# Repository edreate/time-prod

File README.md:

# FocusDock — Focus & Availability Device

A small desk gadget that protects your focus time. It sits on your desk as a
phone dock, or clips onto the top or bottom edge of your monitor. One glance
tells you (and everyone walking by) what's going on:

- **Menu** — pick a program: Focus Timer or Available/Busy. Long-press the
  center click, from anywhere, to jump back to the menu.
- **Focus timer** — set an H:M:S duration, click to start. The screen counts
  down and the LEDs empty out like a progress bar.
- **Status light** — LEDs glow **green** (free), **red** (busy), or **amber**
  (timer running). One click toggles available/busy: an instant meeting
  indicator.
- **Phone dock** — park your phone on it and out of your hands.
- **Mounts either way up** — clip it to the top or bottom monitor edge; the
  screen flips itself the right way up automatically.

## The prototype today

Everything below is running on a breadboard right now:

**Working:** display, motion sensor, auto-flip, LED strip, the menu, focus
timer, pomodoro, and the available/busy status light.
**Not built yet:** Wi-Fi settings, enclosure, proper 5V LED power — see the
[roadmap](#roadmap).

## How to use it

The 5-way button does everything:

| Button | Menu | Setting the timer | Timer running/paused | Availability |
|---|---|---|---|---|
| **Up / Down** | Move cursor | Change selected field | Down = cancel (paused) | — |
| **Left / Right** | — | Select H / M / S field | — | — |
| **Click** (center) | Open program | Start | Pause / resume | Toggle available/busy |
| **Hold click** | — | Return to menu, from any screen | | |

When a focus session hits zero the LEDs blink green and the screen shows
*Done!* — press any button to dismiss.

## What's inside

| Part | Job | ~Price |
|---|---|---|
| ESP32-S3 board (WROOM-1 N16R8) | The brain — runs everything, provides Wi-Fi | €14.49 |
| 1.3" OLED display (128×64, I2C) | Timer and menus | €7.19 |
| BMI160 motion sensor | Detects which way up it's mounted | ~€5 |
| WS2812B LED strip | The status light | €3.89 |
| 5-way button (5DirKey) | All input | ~€1 |

Full wiring instructions, circuit diagram, and part gotchas:
**[docs/HARDWARE.md](docs/HARDWARE.md)**.
New to electronics? Every concept this project uses, explained briefly:
**[docs/ELECTRONICS.md](docs/ELECTRONICS.md)**.

## Build & flash the firmware

You need [Python 3](https://www.python.org/downloads/) and a USB-C cable.
Everything else installs itself.

1. **Plug in the board** and find its port:
   ```
   make ports
   ```
   Yours is one of the `usbmodem*` entries (not `Bluetooth-Incoming-Port` or
   `debug-console`). The board has two USB-C ports — if one doesn't respond,
   try the other. macOS can rename the port across reconnects, so re-check if
   an upload suddenly can't find it.

2. **Flash:**
   ```
   make flash PORT=/dev/cu.usbmodemXXXX
   ```
   The first run installs PlatformIO and downloads the toolchain (~2 min,
   one-time). It then uploads the firmware and opens the serial monitor so you
   can watch the device's log output. `Ctrl+C` exits the monitor.

Other targets: `make build`, `make upload`, `make monitor`, `make clean`.

**If upload hangs at "Connecting..."**: hold **BOOT**, tap **RESET**, release
**BOOT**, retry. If it fails partway with a checksum error, that's a flaky USB
connection — reseat the cable and retry.

### Test firmwares

Besides the main firmware there's a small test build for checking the
hardware — useful after wiring changes. Two boards exist during the
prototype transition (today's N16R8 devkit, and an ESP32-S3 Zero being
evaluated as a smaller replacement — see
[docs/prototype-hardware/README.md](docs/prototype-hardware/README.md)), so
`ENV` picks firmware **and** board:

| `ENV` | What it checks | Board |
|---|---|---|
| `time-prod-app-n16r8` *(default)* | The real firmware — everything | N16R8 devkit |
| `test-peripherals-n16r8` | I2C scan + display + IMU readout: is everything wired and answering? | N16R8 devkit |
| `time-prod-app-s3zero` | The real firmware | ESP32-S3 Zero |
| `test-peripherals-s3zero` | Same hardware check, on the S3 Zero — flash this first on a new S3 Zero board | ESP32-S3 Zero |

Flash it with `make flash ENV=test-peripherals-n16r8 PORT=...` (swap the
`ENV` for whichever board/firmware combination you need).

## Tweaking the firmware

Every tunable number lives in [`src/config.h`](src/config.h): pin assignments,
colors, timer defaults, thresholds. Change a value, `make flash`, done.

The code is split two ways: one header per **peripheral** in `src/hardware/`,
one header per **program** in `src/software/`. `main.cpp` is just the shell —
it owns no hardware and no program state, it routes button events to whichever
program is open and asks it to render.

Adding a sensor is one header in `src/hardware/`; adding a program is one
header in `src/software/` plus a menu row. No build config to touch either way.

Project layout:

```
src/config.h              every tunable (pins, colors, thresholds)
src/hardware/display.h    OLED panel
src/hardware/leds.h       WS2812B status light
src/hardware/imu.h        accelerometer -> screen orientation
src/hardware/buttons.h    5-way switch, debounced
src/software/timer.h      focus timer program
src/software/pomodoro.h   pomodoro program
src/software/availability.h  available / busy program
src/main.cpp              the shell: menu, dispatch, loop
src/test_peripherals.cpp  peripheral check test build
platformio.ini      build configuration (one env per firmware x board)
Makefile            build/upload/monitor shortcuts
docs/HARDWARE.md    parts, wiring, circuit diagram
docs/ELECTRONICS.md electronics concepts, briefly explained
```

## Roadmap

What it takes to go from breadboard to a product with a long life:

**Hardware**
- [ ] Powered by USB only — no battery, no dual-power diode needed
  - [ ] Move LED strip to proper 5V power + 74AHCT125 level shifter +
        1000 µF cap (required at the current 10-LED count, not just at
        scale — exact specs: [HARDWARE.md](docs/HARDWARE.md#level-shifter--capacitor---exact-specs))
- [ ] Supports up to 10 LEDs at max brightness, on a USB 3.0 port (~700-750mA
      draw against USB 3.0's 900mA — see Power notes in HARDWARE.md)
- [ ] Custom PCB once the design settles

**Firmware**
- [ ] One button to instantly switch between available and busy
- [x] Pomodoro program (work / short break / long break, auto-cycling)
- [ ] Settings page over the device's own Wi-Fi hotspot, saved across power-off.
      **Wi-Fi defaults OFF on boot**, menu toggle to enable — its active/TX
      current isn't budgeted into the power target above by default.
- [ ] Wi-Fi client mode (optional, same default-off behavior)
- [ ] Factory-reset gesture (e.g. hold click 10s)
- [ ] Max-brightness LED mode as a menu setting, off by default. Default
      brightness stays at the current power-safe cap (`LED_BRIGHTNESS` in
      `src/config.h`); a menu option raises it for whoever's on a supply
      that can take it, rather than the firmware assuming one globally.
- [ ] Over-the-air firmware updates (optional)

**Product**
- [ ] Session stats (focus minutes per day/week)
- [ ] User-test with non-technical people; simplify anything they stumble on

## License

See [LICENSE](LICENSE).

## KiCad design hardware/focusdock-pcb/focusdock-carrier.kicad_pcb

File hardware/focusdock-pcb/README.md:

# FocusDock Carrier Board

A two-layer carrier PCB that replaces the breadboard wiring in
[`docs/HARDWARE.md`](../../docs/HARDWARE.md). It carries **no bare ICs** — the
ESP32-S3 devkit, OLED, IMU, LED strip and 5-way button all stay as modules and
plug into headers. The board is just the wiring, plus the one passive the
electronics doc asks for (the LED series resistor) and rail decoupling.

Open `focusdock-carrier.kicad_pro` in KiCad 8 or newer (built with 10.0.5).

| | |
|---|---|
| Size | 70 × 50 mm, 3 mm corner radius |
| Layers | 2 (F.Cu / B.Cu), GND pour on both, 59 stitching vias |
| Mounting | 4 × Ø2.7 mm (M2.5), corners |
| Trace widths | 0.25 mm signal, 0.5 mm power |
| ERC | 0 errors, 0 warnings |
| DRC | 0 errors, 0 unconnected pads |

## How the devkit mounts

The ESP32-S3-DevKitC-1 has no bundled KiCad footprint, so it is modelled as
**two 1×22 female sockets** (J1 / J3) that the devkit plugs into like a shield.
The spacing is not a guess — it was measured from Espressif's own mechanical
DXF (`DXF_ESP32-S3-DevKitC-1_V1.1_20220429.dxf`):

| Measurement | Value |
|---|---|
| Header row pitch (J1 ↔ J3) | **22.86 mm** (0.900 in) |
| Pin pitch | 2.54 mm |
| Pins per row | 22 |
| Devkit outline | 62.74 × 25.40 mm |
| Devkit drill | Ø1.02 mm |

Pin 1 of both rows is at the **antenna** end; the USB ports are at the pin-22
end. The devkit body spans roughly x 21.5–84.3, y 38.7–64.1 on this board, so
every peripheral connector sits *above* it and stays reachable once the devkit
is seated.

## Connectors

Pin 1 is the square pad on every header. Full legend is also printed on the
back silkscreen.

| Ref | Part | Pins (1 → n) |
|---|---|---|
| **J1** | Devkit socket, row J1 | `3V3 3V3 RST 4 5 6 7 15 16 17 18 8 3 46 9 10 11 12 13 14 5V G` |
| **J3** | Devkit socket, row J3 | `G TX RX 1 2 42 41 40 39 38 37 36 35 0 45 48 47 21 20 19 G G` |
| **J2** | OLED, 1×4 | `VDD GND SCK SDA` |
| **J4** | BMI160 IMU, 1×12 | `VIN NC GND SCL SDA SA0 CS NC NC NC NC NC` |
| **J5** | WS2812B strip, 1×3 | `VDD DIN GND` |
| **J6** | 5DirKey V1-2, 1×6 | `GND F B L R CLICK` |

`J6` pins are named by the button module's **physical silkscreen** (F/B/L/R),
not the logical directions the firmware uses — `buttonsPoll()` in
`src/hardware/buttons.h` does that remap. See the button-mapping section of
[`CLAUDE.md`](../../CLAUDE.md).

## Net map

Matches the wiring table in `docs/HARDWARE.md` pin for pin.

| Net | Devkit pin | Goes to |
|---|---|---|
| `+3V3` | J1/1, J1/2 | J2/1, J4/1 (VIN), J4/7 (CS, tied high for I2C mode), JP1/1, C1, C2 |
| `GND` | J1/22, J3/1, J3/21, J3/22 | pour → every module ground, J4/6 (SA0 → 0x68) |
| `I2C_SDA` | J1/12 (GPIO8) | J2/4, J4/5 |
| `I2C_SCL` | J1/15 (GPIO9) | J2/3, J4/4 |
| `LED_DATA` | J1/9 (GPIO16) | R1 (330 Ω) |
| `LED_DIN` | — | R1 → J5/2 |
| `LED_VDD` | — | JP1/2 → J5/1, C3 |
| `+5V` | J1/21 | JP1/3 |
| `BTN_F` | J1/4 (GPIO4) | J6/2 |
| `BTN_B` | J1/5 (GPIO5) | J6/3 |
| `BTN_L` | J1/6 (GPIO6) | J6/4 |
| `BTN_R` | J1/7 (GPIO7) | J6/5 |
| `BTN_CLICK` | J1/8 (GPIO15) | J6/6 |

`J4/2` (the BMI160 breakout's `3V3` pin) is deliberately left unconnected — it
is the module regulator's *output*, and driving it is the mistake
`docs/HARDWARE.md` warns about. All other IMU aux pins (INT1/INT2/OCS/SCX/SDX)
are unconnected too, as are the 19 devkit GPIOs the firmware doesn't use.

## JP1 — LED supply selector

`docs/HARDWARE.md` runs the WS2812B at 3.3 V for bring-up but notes 5 V is the
real spec. JP1 makes that a solder-jumper choice instead of a board respin:

```
  +3V3  1 ──┐
            ├── 2  LED_VDD  →  J5/1, C3
   +5V  3 ──┘
```

Ships with **1–2 bridged (3.3 V)**, matching the current firmware and docs. To
move to 5 V, cut the 1–2 bridge and solder 2–3 — and read the power note in
`docs/HARDWARE.md` first: at 5 V the 3.3 V data line is marginal and wants the
74AHCT125 level shifter that is still on the roadmap.

## Files

```
focusdock-carrier.kicad_pro/.kicad_sch/.kicad_pcb   the project
export/                                            SVG + PNG previews
fab/gerbers/                                       gerbers + Excellon drill
fab/focusdock-carrier-bom.csv                      BOM
fab/focusdock-carrier-pos.csv                      pick-and-place
```

`fab/` is generated output — regenerate it from the project rather than
editing it.

## Before you order

- **Verify the J4 pin order against your actual BMI160 breakout.** The board is
  wired for the common GY-BMI160 12-pin order listed above. Breakouts sold under
  the same name do vary; a mismatch makes that one connector wrong.
- The four `MountingHole_2.7mm` DRC warnings ("does not match copy in library")
  are cosmetic — the footprints were created as local variants.
- No enclosure dimensions were available, so the outline is a plain rounded
  rectangle sized to the devkit. The monitor-clip / phone-dock mechanics in the
  README roadmap are not accounted for.

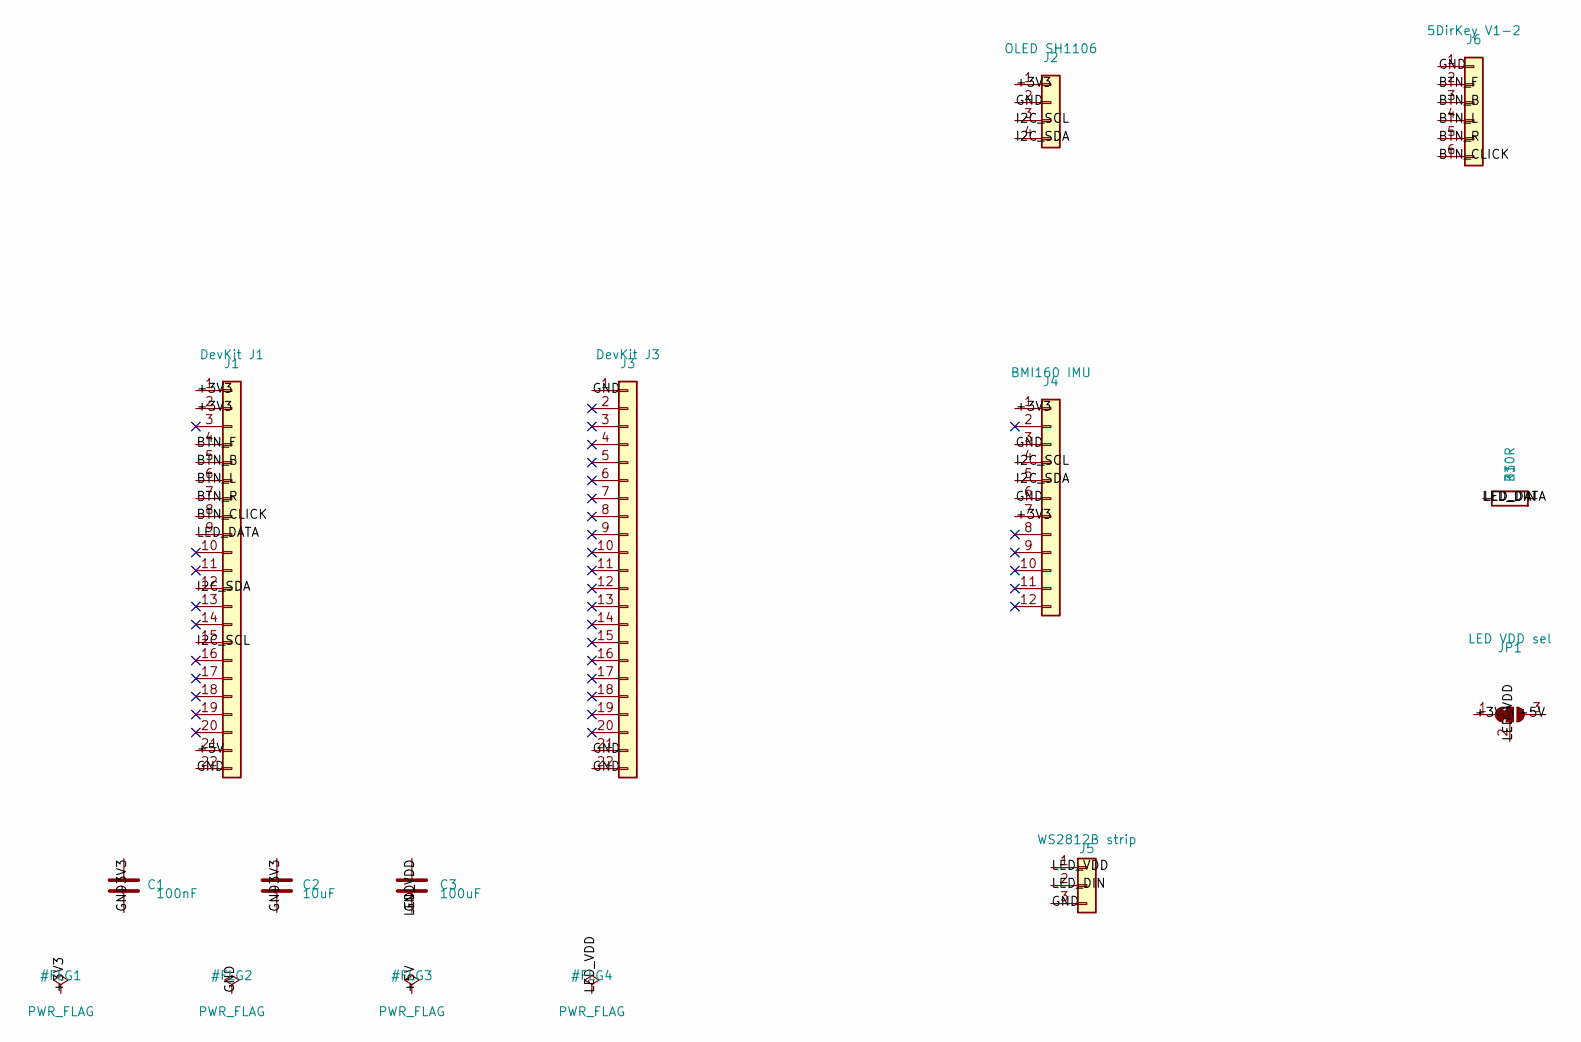
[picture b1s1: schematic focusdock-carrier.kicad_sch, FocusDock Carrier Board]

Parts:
C1: 100nF; C_0805_2012Metric
C2: 10uF; C_0805_2012Metric
C3: 100uF; C_1206_3216Metric
J1: DevKit J1; PinSocket_1x22_P2.54mm_Vertical
J2: OLED SH1106; PinSocket_1x04_P2.54mm_Vertical
J3: DevKit J3; PinSocket_1x22_P2.54mm_Vertical
J4: BMI160 IMU; PinSocket_1x12_P2.54mm_Vertical
J5: WS2812B strip; PinSocket_1x03_P2.54mm_Vertical
J6: 5DirKey V1-2; PinSocket_1x06_P2.54mm_Vertical
JP1: LED VDD sel; SolderJumper-3_P1.3mm_Bridged12_RoundedPad1.0x1.5mm
R1: 330R; R_0805_2012Metric

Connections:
+3V3: C1.1, C2.1, J1.1, J1.2, J2.1, J4.1, J4.7, JP1.1 (A)
+5V: J1.21, JP1.3 (B)
BTN_B: J1.5, J6.3
BTN_CLICK: J1.8, J6.6
BTN_F: J1.4, J6.2
BTN_L: J1.6, J6.4
BTN_R: J1.7, J6.5
GND: C1.2, C2.2, C3.2, J1.22, J2.2, J3.1, J3.21, J3.22, J4.3, J4.6, J5.3, J6.1
I2C_SCL: J1.15, J2.3, J4.4
I2C_SDA: J1.12, J2.4, J4.5
LED_DATA: J1.9, R1.1
LED_DIN: J5.2, R1.2
LED_VDD: C3.1, J5.1, JP1.2 (C)

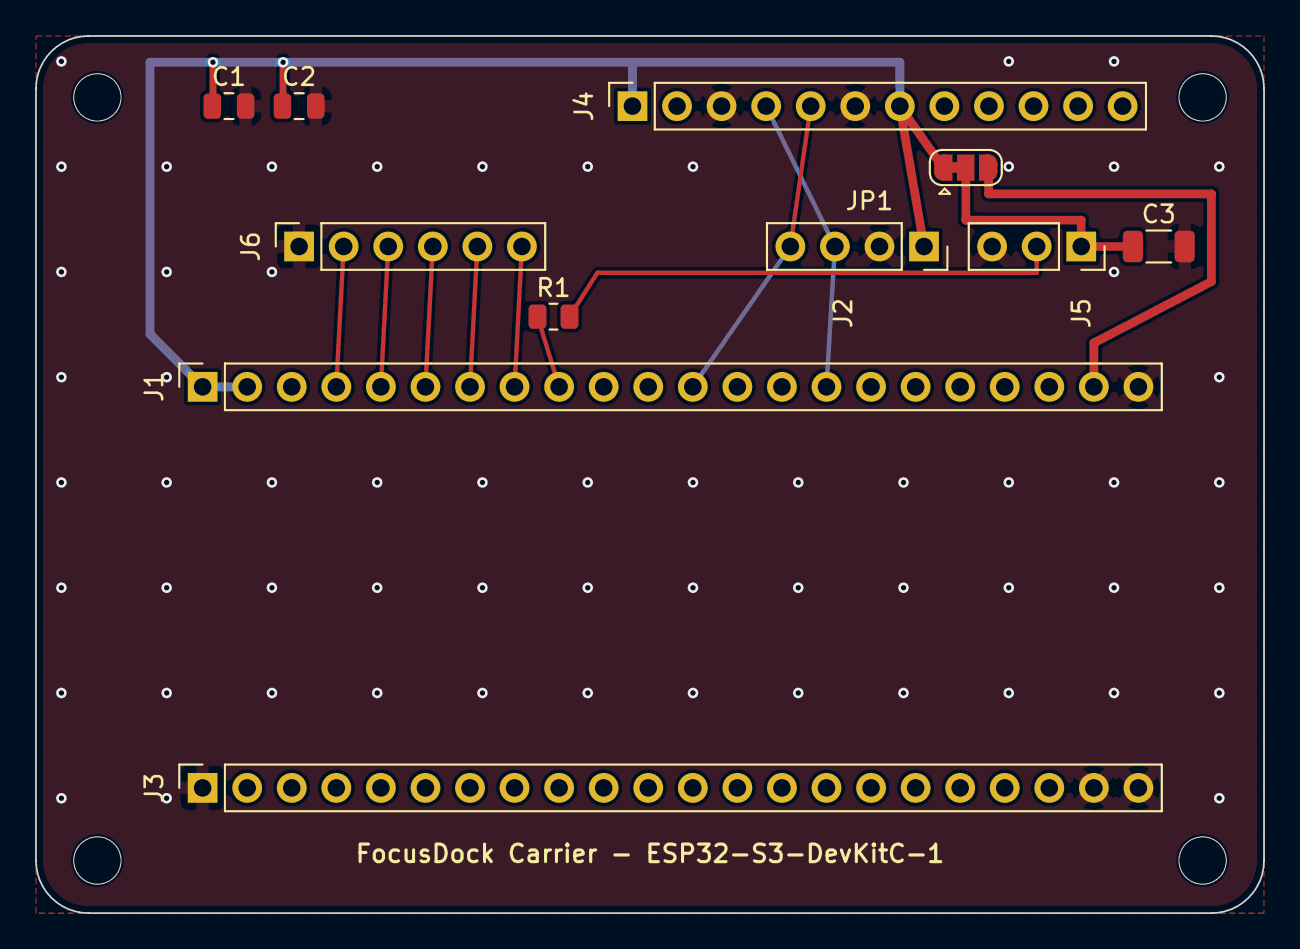
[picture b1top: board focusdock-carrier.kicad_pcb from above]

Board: 2 copper layers, 70.0 x 50.0 mm, 15 parts (0 on the bottom side), 13 nets.

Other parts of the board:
MH1, MH2, MH3, MH4: MountingHole_2.7mm

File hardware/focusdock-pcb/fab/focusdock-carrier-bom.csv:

value,footprint,quantity,references
DevKit J3,Connector_PinSocket_2.54mm:PinSocket_1x22_P2.54mm_Vertical,1,['J3']
MountingHole_2.7mm,MountingHole:MountingHole_2.7mm,4,"['MH1', 'MH4', 'MH2', 'MH3']"
100uF,Capacitor_SMD:C_1206_3216Metric,1,['C3']
LED VDD sel,Jumper:SolderJumper-3_P1.3mm_Bridged12_RoundedPad1.0x1.5mm,1,['JP1']
100nF,Capacitor_SMD:C_0805_2012Metric,1,['C1']
BMI160 IMU,Connector_PinSocket_2.54mm:PinSocket_1x12_P2.54mm_Vertical,1,['J4']
DevKit J1,Connector_PinSocket_2.54mm:PinSocket_1x22_P2.54mm_Vertical,1,['J1']
OLED SH1106,Connector_PinSocket_2.54mm:PinSocket_1x04_P2.54mm_Vertical,1,['J2']
WS2812B strip,Connector_PinSocket_2.54mm:PinSocket_1x03_P2.54mm_Vertical,1,['J5']
5DirKey V1-2,Connector_PinSocket_2.54mm:PinSocket_1x06_P2.54mm_Vertical,1,['J6']
10uF,Capacitor_SMD:C_0805_2012Metric,1,['C2']
330R,Resistor_SMD:R_0805_2012Metric,1,['R1']

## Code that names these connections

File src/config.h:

// Every tunable in the firmware - pins, colors, defaults, thresholds.
// This is the one place to re-map hardware; nothing below it hardcodes a pin.
#pragma once

// ---- pins / I2C ----
#define PIN_I2C_SDA 8
#define PIN_I2C_SCL 9
#define PIN_LED_DATA 16
#define PIN_BTN_F 4 // physical "F" -> logical LEFT
#define PIN_BTN_B 5 // physical "B" -> logical RIGHT
#define PIN_BTN_L 6 // physical "L" -> logical DOWN
#define PIN_BTN_R 7 // physical "R" -> logical UP
#define PIN_BTN_PRESS 15
#define IMU_I2C_ADDR 0x68 // not BMI160_I2C_ADDR - the driver library owns that name

// ---- LEDs / colors ----
#define NUM_LEDS 10              // 10 LEDs = one per 10% of the timer
#define LED_BRIGHTNESS 60        // 0-255; capped low on purpose (power budget)
#define COLOR_AVAILABLE 0x00FF00 // green = free
#define COLOR_BUSY 0xFF0000      // red   = busy
#define COLOR_PROGRESS 0xFFA500  // amber = timer running
#define COLOR_DONE 0x00FF00      // green = timer done, blinking
#define COLOR_OFF 0x000000
#define DONE_BLINK_MS 500

// ---- pomodoro ----
#define COLOR_POMO_WORK 0xFF0000        // red   = work phase, do not disturb
#define COLOR_POMO_SHORT_BREAK 0x00FF00 // green = short break
#define COLOR_POMO_LONG_BREAK 0x0080FF  // blue  = long break
#define DEFAULT_POMO_WORK_MIN 25
#define DEFAULT_POMO_SHORT_MIN 5
#define DEFAULT_POMO_LONG_MIN 15
#define DEFAULT_POMO_SESSIONS 4         // work sessions before a long break
#define POMO_PHASE_TRANSITION_MS 3000   // blink window before auto-continuing

// ---- buttons ----
#define BTN_DEBOUNCE_MS 30
#define LONG_PRESS_MS 800 // hold this long anywhere -> back to menu

// ---- timer defaults ----
#define DEFAULT_HOURS 0
#define DEFAULT_MINUTES 25 // classic pomodoro length
#define DEFAULT_SECONDS 0

// ---- orientation ----
#define FLIP_THRESHOLD 0.5f  // g; accel-x past +/- this commits a state
#define FLIP_DEBOUNCE_MS 350 // must hold past threshold this long
#define EMA_ALPHA 0.2f       // accel smoothing, 0..1 (higher = jumpier)

// ---- loop / display ----
#define LOOP_DELAY_MS 10
#define DISPLAY_REDRAW_MS 100
#define PROGRESS_CHARS 10 // width of the on-screen timer bar, in characters
